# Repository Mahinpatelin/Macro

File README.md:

# Macro — Custom RP2040 Macropad

An end-to-end mechatronics build combining PCB design, embedded firmware, human-machine-interface design, and a 3D-printed enclosure. The device uses eight mechanical keys, an EC11 rotary encoder with push switch, an OLED header, and a Seeed Studio XIAO RP2040.

> Status: design package complete; fabrication outputs are included. Hardware behavior must be verified on the physical assembly before the design is treated as production-ready.

## Engineering highlights

- Designed a custom 2 × 5 electrical key matrix in KiCad with one intentionally unpopulated matrix position.
- Added per-switch diodes to prevent ghosting during multi-key input.
- Integrated an RP2040 microcontroller, incremental encoder, encoder push switch, and I²C OLED connector.
- Implemented QMK firmware for key scanning, volume control, mute, and OLED status.
- Packaged Gerber fabrication files and an STL enclosure for reproducible manufacturing.
- Added an automated design audit that cross-checks PCB population against the QMK layout.

## Repository map

| Path | Purpose |
|---|---|
| `PCB/` | Editable KiCad schematic and PCB sources |
| `CAD/case.stl` | Printable enclosure mesh |
| `Production/gerbers.zip` | PCB manufacturing outputs |
| `macro_firmware/` | QMK keyboard definition and keymap |
| `docs/BOM.csv` | Bill of materials |
| `docs/DESIGN.md` | Requirements, architecture, and engineering decisions |
| `docs/BUILD_GUIDE.md` | Fabrication, assembly, flashing, and bring-up |
| `tools/design_audit.py` | PCB/firmware consistency checks |

## Quick validation

```bash
python3 tools/design_audit.py
```

The audit checks the eight Cherry MX footprints, encoder switch, nine diodes, matrix dimensions, and nine populated QMK positions. It does not replace electrical-rule checking, design-rule checking, or physical bring-up.

## Firmware build

1. Install the [QMK CLI](https://docs.qmk.fm/newbs_getting_started).
2. Copy `macro_firmware` into a keyboard folder in a QMK checkout.
3. Compile the default keymap for the RP2040 target.
4. Enter the XIAO RP2040 bootloader and copy the generated UF2 file to the board.

Exact commands depend on the folder name chosen inside the QMK tree. See [the build guide](docs/BUILD_GUIDE.md) before connecting hardware.

## Design correction documented in this version

The PCB contains eight Cherry MX switches plus the encoder push switch: nine physical buttons total. The original firmware layout declared all ten positions of the 2 × 5 matrix and assigned a key to the unpopulated position. This version models only the nine populated positions while retaining the 2 × 5 electrical matrix.

## Skills demonstrated

PCB design · embedded C · QMK · RP2040 · matrix scanning · design for manufacture · CAD-to-print workflow · engineering validation

## Safety and limitations

- Confirm polarity, continuity, and supply rails with a multimeter before inserting the microcontroller.
- Verify the OLED module voltage and pin order; common modules do not all share the same header order.
- Gerbers should be re-generated after any PCB source change.
- The included STL should be checked against the chosen printer, switch plate, fasteners, and tolerances.

## License

Original firmware, documentation, and project-specific design files are released under the MIT License. Third-party footprints, libraries, and tools retain their respective licenses.

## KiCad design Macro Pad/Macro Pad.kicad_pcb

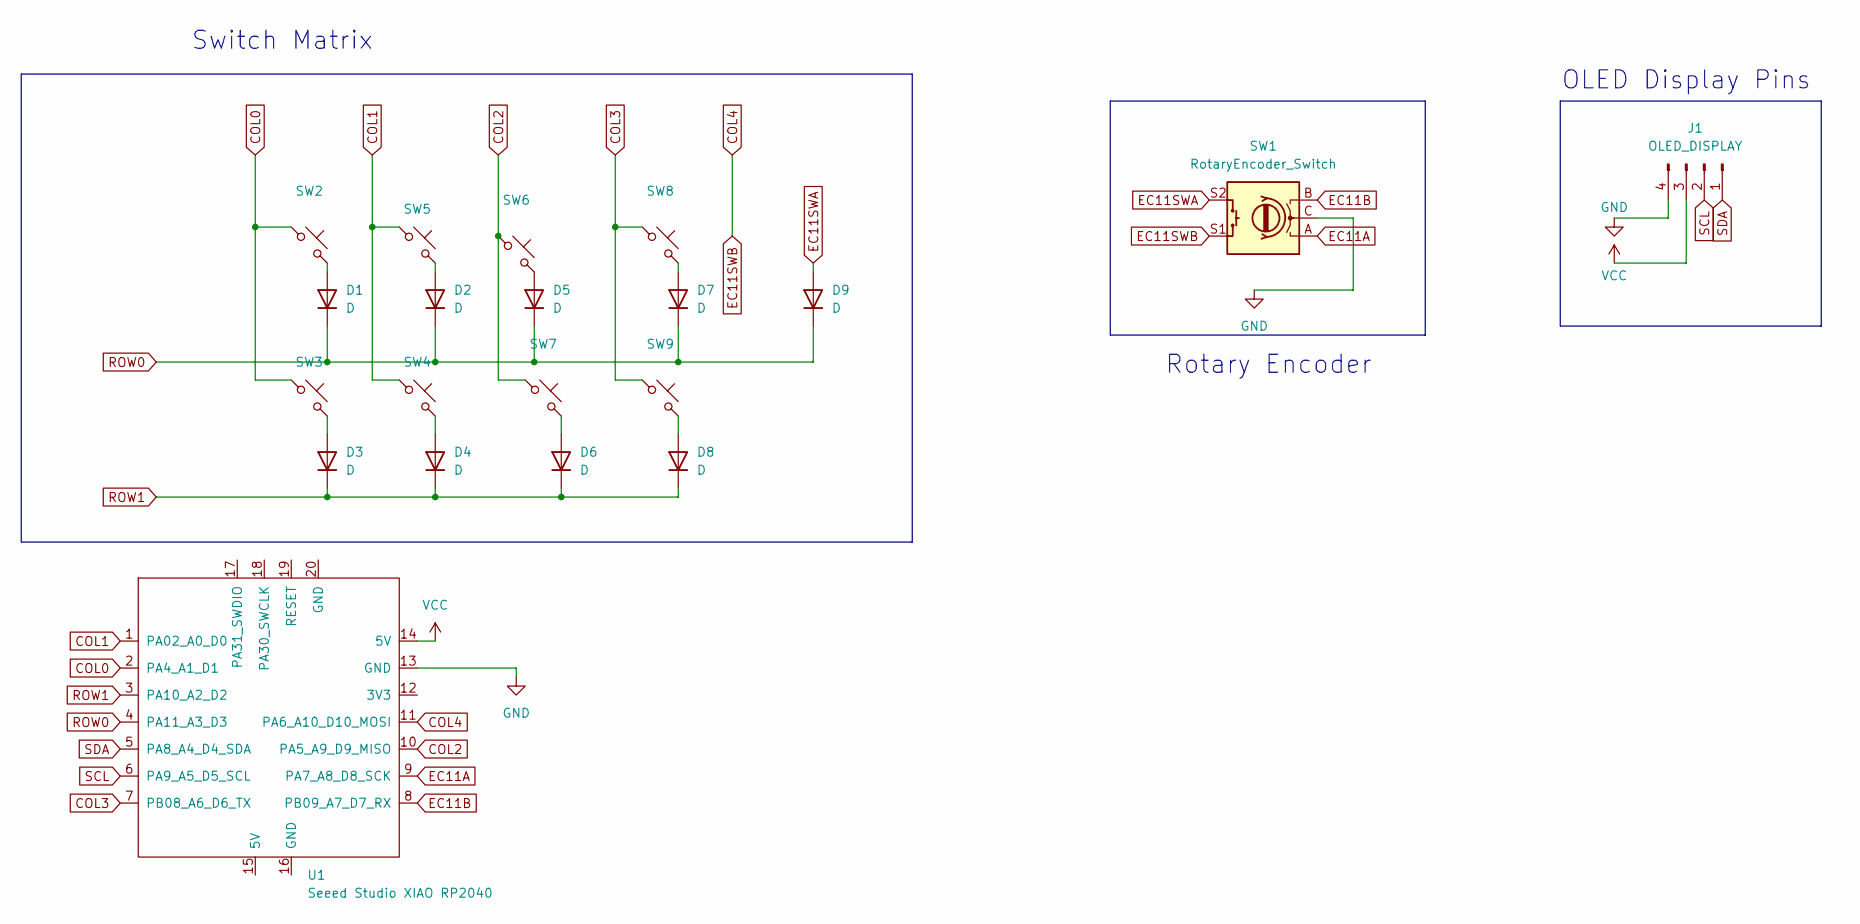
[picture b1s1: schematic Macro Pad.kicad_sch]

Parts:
D1, D2, D3, D4, D5, D6, D7, D8, D9: D; D_DO-35_SOD27_P7.62mm_Horizontal
J1: OLED_DISPLAY; PinHeader_1x04_P2.54mm_Vertical
SW1: RotaryEncoder_Switch; RotaryEncoder_Alps_EC11E-Switch_Vertical_H20mm
SW2, SW3, SW4, SW5, SW6, SW7, SW8, SW9: SW_Push_45deg; SW_Cherry_MX_1.00u_PCB
U1: Seeed Studio XIAO RP2040; XIAO-Generic-Hybrid-14P-2.54-21X17.8MM

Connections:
COL0: SW2.1, SW3.1, U1.2 (PA4_A1_D1)
COL1: SW4.1, SW5.1, U1.1 (PA02_A0_D0)
COL2: SW6.1, SW7.1, U1.10 (PA5_A9_D9_MISO)
COL3: SW8.1, SW9.1, U1.7 (PB08_A6_D6_TX)
COL4: SW1.S1, U1.11 (PA6_A10_D10_MOSI)
EC11A: SW1.A, U1.9 (PA7_A8_D8_SCK)
EC11B: SW1.B, U1.8 (PB09_A7_D7_RX)
EC11SWA: D9.2 (A), SW1.S2
GND: J1.4, SW1.C, U1.13 (GND)
unnamed: D1.2 (A), SW2.2
unnamed: D2.2 (A), SW5.2
unnamed: D3.2 (A), SW3.2
unnamed: D4.2 (A), SW4.2
unnamed: D5.2 (A), SW6.2
unnamed: D6.2 (A), SW7.2
unnamed: D7.2 (A), SW8.2
unnamed: D8.2 (A), SW9.2
ROW0: D1.1 (K), D2.1 (K), D5.1 (K), D7.1 (K), D9.1 (K), U1.4 (PA11_A3_D3)
ROW1: D3.1 (K), D4.1 (K), D6.1 (K), D8.1 (K), U1.3 (PA10_A2_D2)
SCL: J1.2, U1.6 (PA9_A5_D5_SCL)
SDA: J1.1, U1.5 (PA8_A4_D4_SDA)
VCC: J1.3, U1.14 (5V)

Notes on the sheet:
Switch Matrix
OLED Display Pins
Rotary Encoder

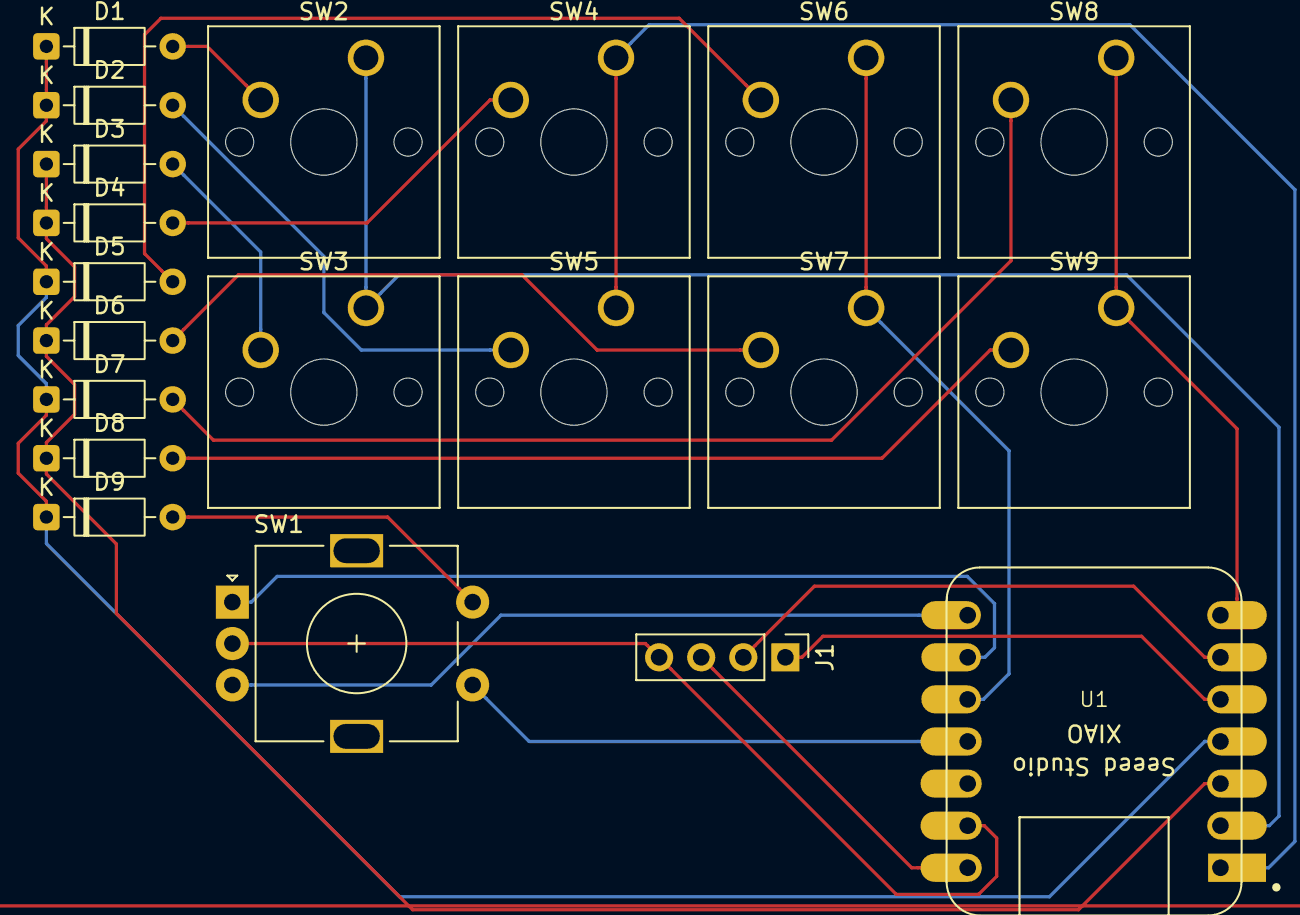
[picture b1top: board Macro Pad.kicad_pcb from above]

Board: 2 copper layers, 20 parts (0 on the bottom side), 22 nets.
